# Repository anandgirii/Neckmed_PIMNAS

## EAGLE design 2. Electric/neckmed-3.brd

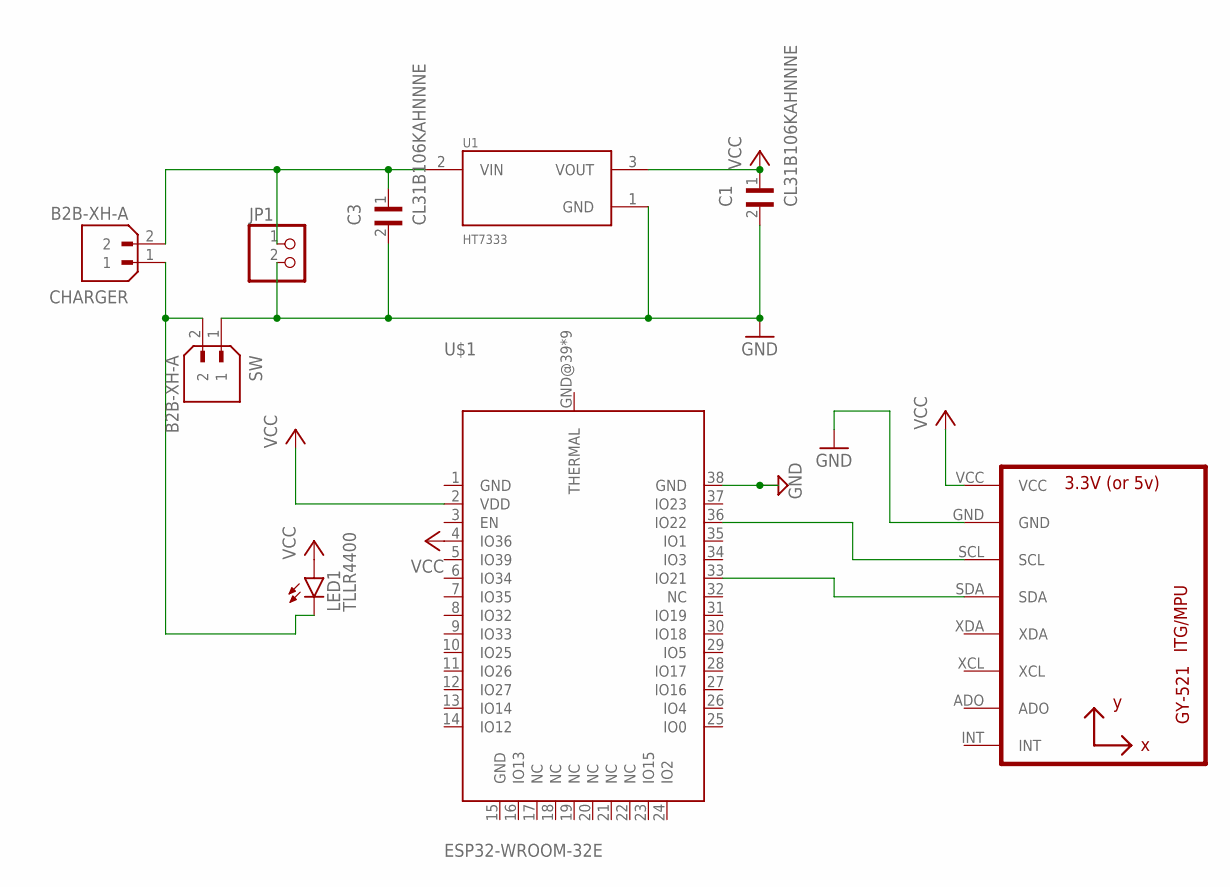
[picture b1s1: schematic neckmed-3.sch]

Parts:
C1, C3: CL31B106KAHNNNE; CAPC3216X180N
CHARGER: B2B-XH-A; JST_B2B-XH-A
JP1: PINHD-1X2; 1X02
LED1: TLLR4400; LED3MM
SW: B2B-XH-A; JST_B2B-XH-A
U1: HT7333; IC_HT7333
U2: GY-521MPU6050; GY-521
U$1: ESP32-WROOM-32E

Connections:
GND: C1.2, C3.2, JP1.2, SW.1, U1.1 (GND), U2.GND, U$1.38 (GND)
unnamed: C3.1, CHARGER.2, JP1.1, U1.2 (VIN)
unnamed: CHARGER.1, LED1.K (C), SW.2
unnamed: U2.SCL, U$1.36 (IO22)
unnamed: U2.SDA, U$1.33 (IO21)
VCC: C1.1, LED1.A, U1.3 (VOUT), U2.VCC, U$1.2 (VDD), U$1.4 (IO36)

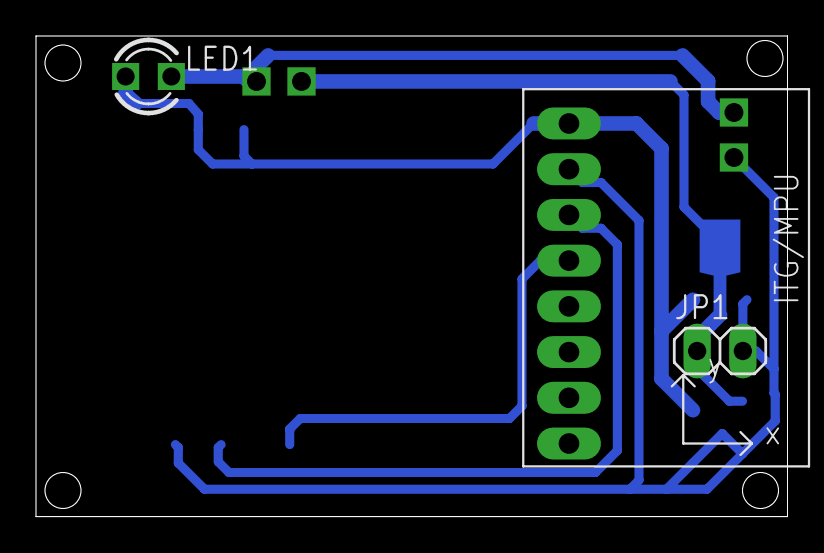
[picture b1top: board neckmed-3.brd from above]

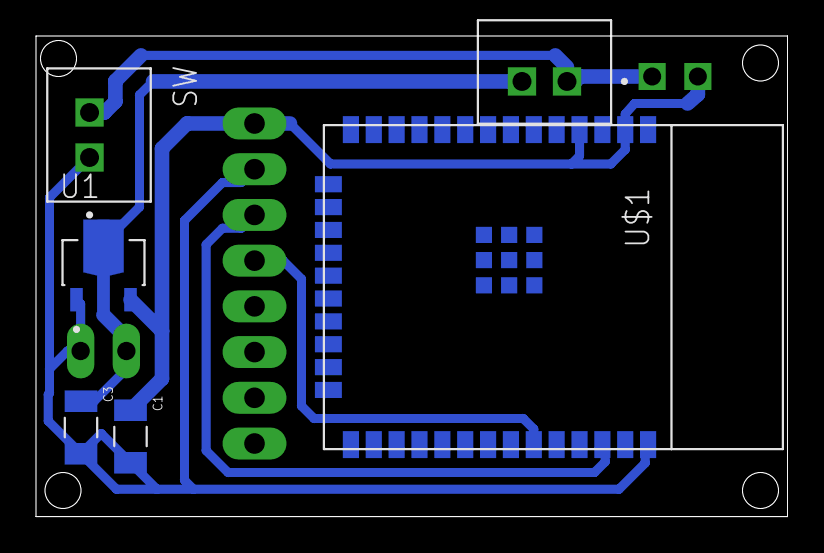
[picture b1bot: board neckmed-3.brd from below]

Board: 2 copper layers, 41.8 x 26.7 mm, 9 parts (6 on the bottom side), 6 nets.

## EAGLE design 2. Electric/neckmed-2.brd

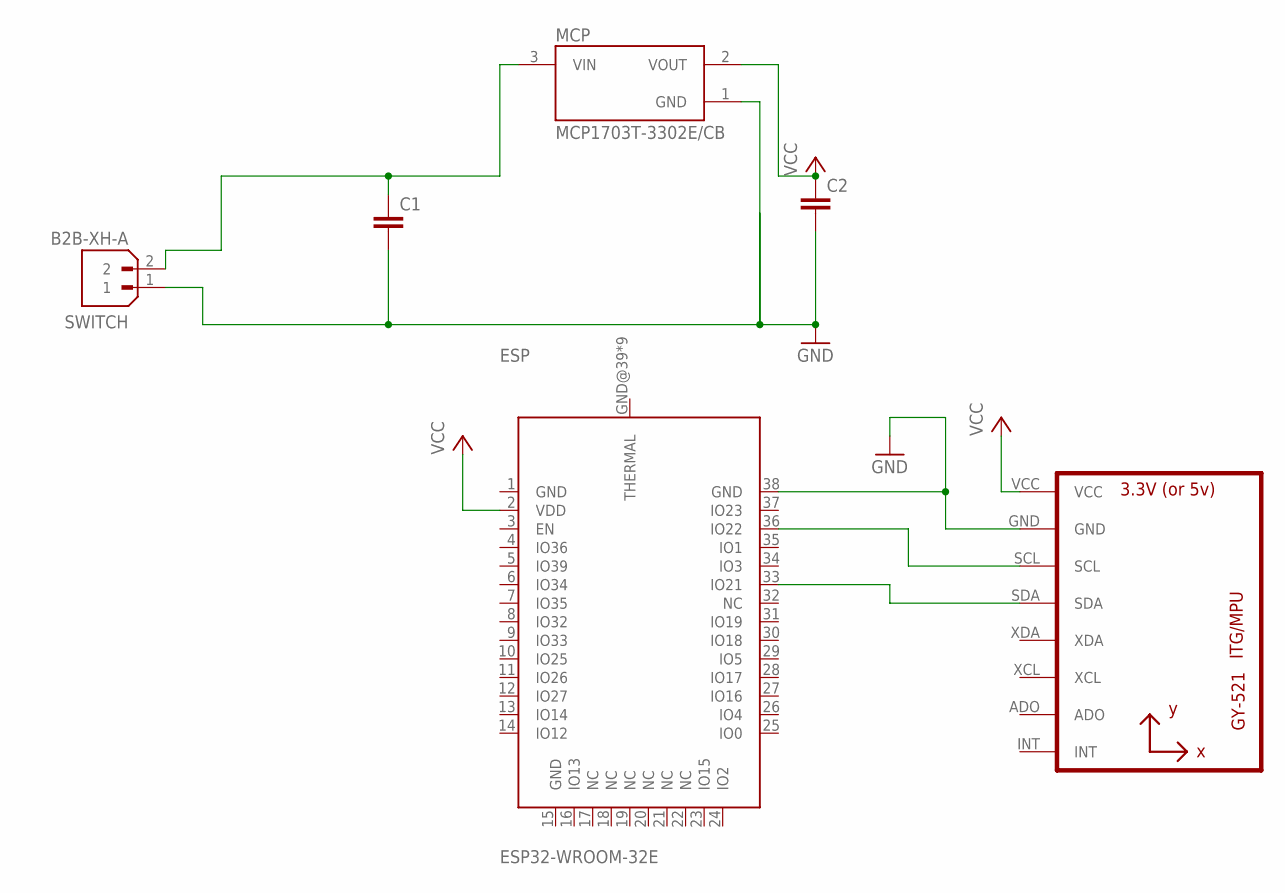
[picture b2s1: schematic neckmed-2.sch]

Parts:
C1, C2: C-EU025-040X050; C025-040X050
ESP: ESP32-WROOM-32E
GY: GY-521MPU6050; GY-521
MCP: MCP1703T-3302E/CB; SOT95P255X145-3N
SWITCH: B2B-XH-A; JST_B2B-XH-A

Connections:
GND: C1.2, C2.2, ESP.38 (GND), GY.GND, MCP.1 (GND), SWITCH.1
unnamed: C1.1, MCP.3 (VIN), SWITCH.2
unnamed: ESP.36 (IO22), GY.SCL
unnamed: ESP.33 (IO21), GY.SDA
VCC: C2.1, ESP.2 (VDD), GY.VCC, MCP.2 (VOUT)

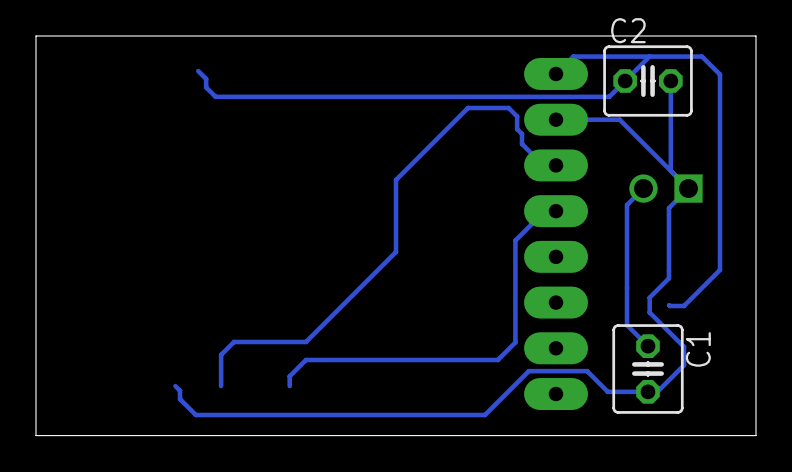
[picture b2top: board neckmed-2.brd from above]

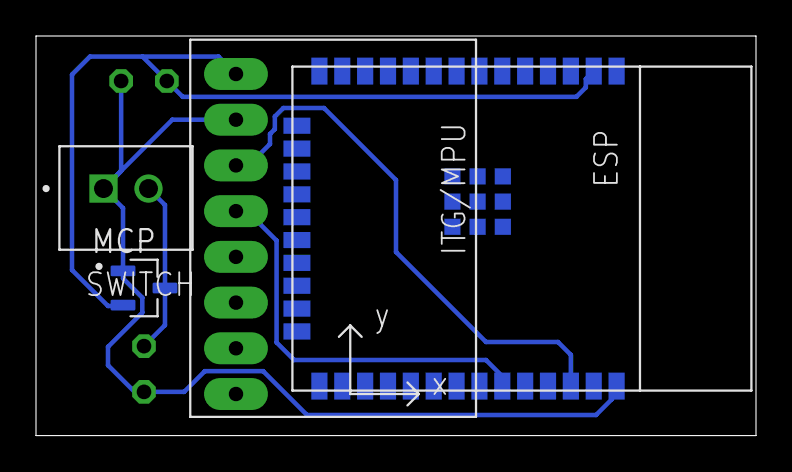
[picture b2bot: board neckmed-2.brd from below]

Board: 2 copper layers, 40.0 x 22.2 mm, 6 parts (4 on the bottom side), 5 nets.
